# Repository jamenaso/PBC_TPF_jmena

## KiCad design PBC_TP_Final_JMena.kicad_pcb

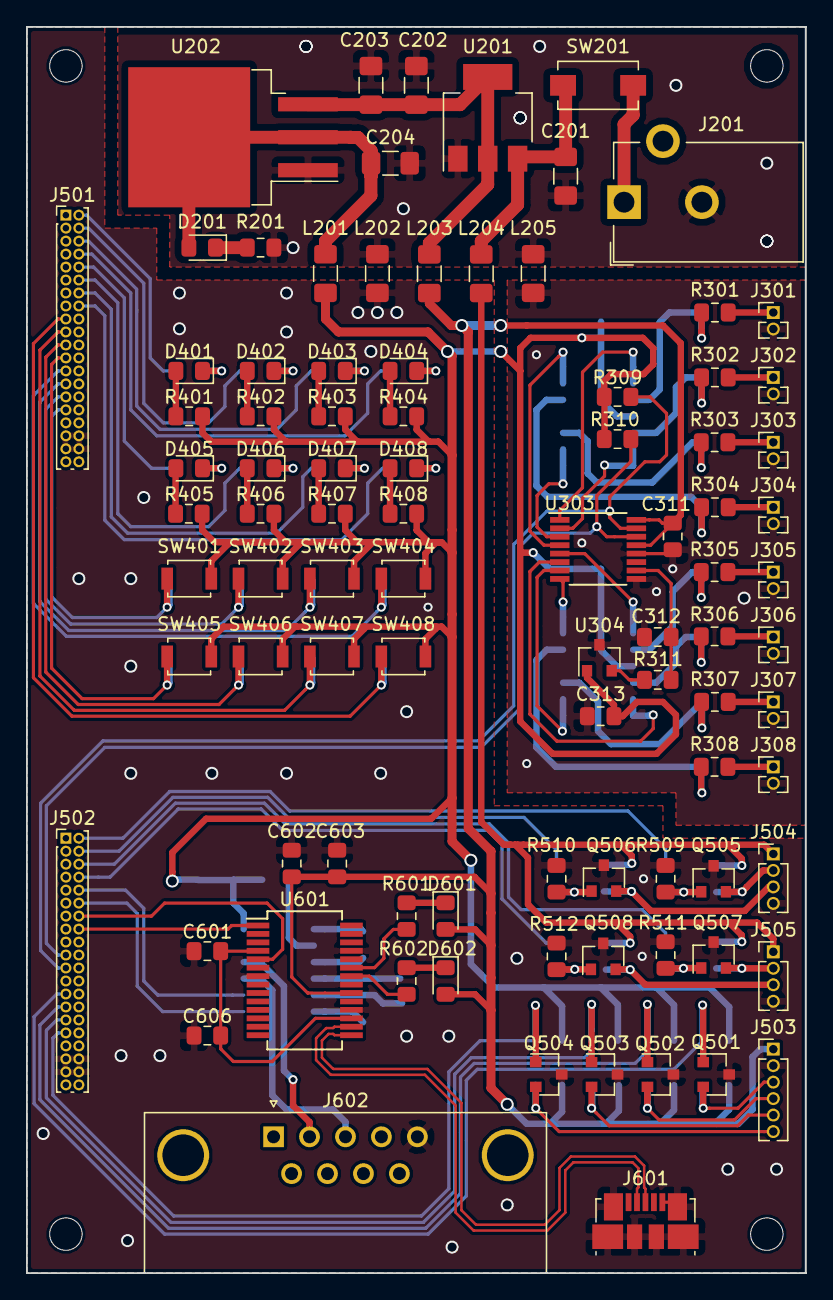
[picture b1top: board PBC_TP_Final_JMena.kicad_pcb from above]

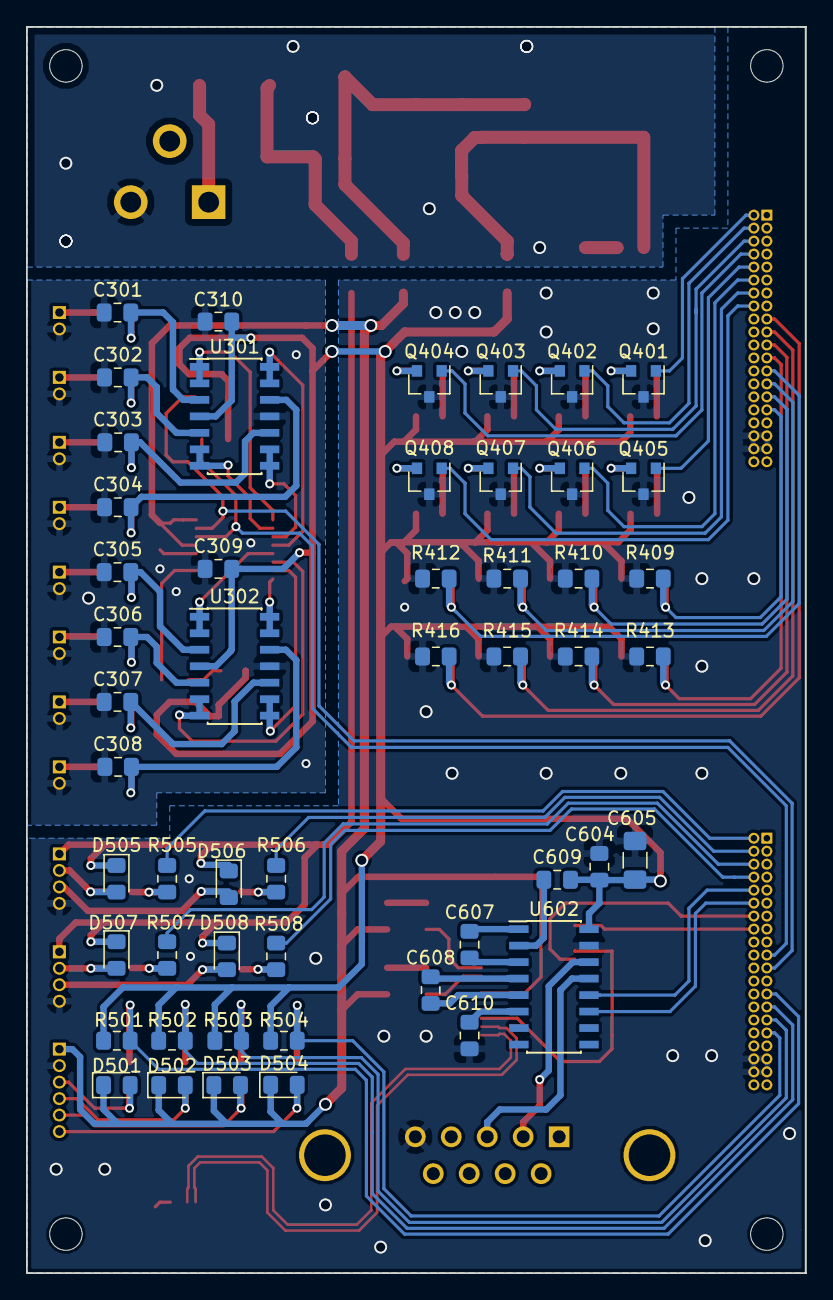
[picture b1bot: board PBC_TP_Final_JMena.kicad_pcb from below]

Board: 2 copper layers, 60.0 x 96.0 mm, 146 parts (51 on the bottom side), 110 nets.

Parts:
C201, C202, C203, C204: 10uF; C_1206_3216Metric_Pad1.42x1.75mm_HandSolder
C301, C302, C303, C304, C305, C306, C307, C308, C312, C603: 1uF; C_0805_2012Metric_Pad1.15x1.40mm_HandSolder
C309, C310, C311, C313, C601, C602, C604, C606, C607, C608, C609, C610: 0.1uF; C_0805_2012Metric_Pad1.15x1.40mm_HandSolder
C605: 2.2uF; C_1206_3216Metric_Pad1.42x1.75mm_HandSolder
D201, D401, D402, D403, D404, D405, D406, D407, D408, D601, D602: LED; LED_0805_2012Metric_Pad1.15x1.40mm_HandSolder
D501, D502, D503, D504, D505, D506, D507, D508: D_Schottky; D_0805_2012Metric_Pad1.15x1.40mm_HandSolder
J201: Barrel_Jack; BarrelJack_CUI_PJ-102AH_Horizontal
J301, J302, J303, J304, J305, J306, J307, J308: Conn_01x02_Female; PinHeader_1x02_P1.27mm_Vertical
J501, J502: Conn_01x40_Male; PinHeader_2x20_P1.00mm_Vertical
J503: Conn_01x06_Male; PinHeader_1x06_P1.27mm_Vertical
J504, J505: Conn_01x04; PinHeader_1x04_P1.27mm_Vertical
J601: USB_B_Micro; USB_Micro-B_Molex_47346-0001
J602: DB9_Male; DSUB-9_Male_Horizontal_P2.77x2.84mm_EdgePinOffset7.70mm_Hou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
L201, L202, L203, L204, L205: Ferrite_Bead; L_1206_3216Metric_Pad1.42x1.75mm_HandSolder
MH101, MH102, MH103, MH104: MountingHole; MountingHole_2.5mm
Q401, Q402, Q403, Q404, Q405, Q406, Q407, Q408, Q501, Q502, Q503, Q504, Q505, Q506, Q507, Q508: FDV301N; SOT-23
R201: 220; R_0805_2012Metric_Pad1.15x1.40mm_HandSolder
R301, R302, R303, R304, R305, R306, R307, R308: 10; R_0805_2012Metric_Pad1.15x1.40mm_HandSolder
R309, R310: 750; R_0805_2012Metric_Pad1.15x1.40mm_HandSolder
R311: 0; R_0805_2012Metric_Pad1.15x1.40mm_HandSolder
R401, R402, R403, R404, R405, R406, R407, R408: 470; R_0805_2012Metric_Pad1.15x1.40mm_HandSolder
R409, R410, R411, R412, R413, R414, R415, R416, R501, R502, R503, R504, R505, R506, R507, R508, R509, R510, R511, R512: 1K; R_0805_2012Metric_Pad1.15x1.40mm_HandSolder
R601, R602: 1K5; R_0805_2012Metric_Pad1.15x1.40mm_HandSolder
SW201: SW_DIP_x01; SW_SPST_EVQPE1
SW401, SW402, SW403, SW404, SW405, SW406, SW407, SW408: SW_Push; SW_SPST_B3U-1000P
U201: NCP1117-5.0_SOT223; SOT-223-3_TabPin2
U202: LM1084-3.3; TO-263-3_TabPin2
U301, U302: LM324; SOIC-14_3.9x8.7mm_P1.27mm
U303: ADS7828; TSSOP-16_4.4x5mm_P0.65mm
U304: MCP1525-TT; SOT-23
U601: FT232RL; SSOP-28_5.3x10.2mm_P0.65mm
U602: MAX3232; SOIC-16_3.9x9.9mm_P1.27mm

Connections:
+3V3: C309.1, C310.1, C313.1, C604.1, C605.1, C609.1, L201.1, R309.1, R310.1, R401.1, R402.1, R403.1, R404.1, R405.1, R406.1, R407.1, R408.1, R501.1, R502.1, R503.1, R504.1, SW401.2, SW402.2, SW403.2, SW404.2, SW405.2, SW406.2, SW407.2, SW408.2, U301.4, U302.4, U304.1, U602.16
+5V: C311.1, C602.1, C603.1, D501.1, D502.1, D503.1, D504.1, D601.2, D602.2, J503.1, L203.1, U303.13, U303.16, U601.20
+12V: D505.1, D506.1, D507.1, D508.1, J504.1, J505.1, L204.1
/Comunicación/COMM0: J502.16, U601.1
/Comunicación/COMM1: J502.14, U601.5
/Comunicación/COMM2: J502.12, U602.11
/Comunicación/COMM3: J502.10, U602.12
/Comunicación/D+: J601.3, U601.15
/Comunicación/D-: J601.2, U601.16
/Comunicación/RS232_RxIn: J602.3, U602.13
/Comunicación/RS232_TxOut: J602.2, U602.14
/Conversión Analogo-Digital/CH0: U301.1, U301.2, U303.1
/Conversión Analogo-Digital/CH1: U301.6, U301.7, U303.2
/Conversión Analogo-Digital/CH2: U301.8, U301.9, U303.3
/Conversión Analogo-Digital/CH3: U301.13, U301.14, U303.4
/Conversión Analogo-Digital/CH4: U302.1, U302.2, U303.5
/Conversión Analogo-Digital/CH5: U302.6, U302.7, U303.6
/Conversión Analogo-Digital/CH6: U302.8, U302.9, U303.7
/Conversión Analogo-Digital/CH7: U302.13, U302.14, U303.8
/Conversión Analogo-Digital/I2C0: J502.19, R310.2, U303.14
/Conversión Analogo-Digital/I2C1: J502.21, R309.2, U303.15
/Conversión Analogo-Digital/VREF: C312.1, R311.1, U303.10
/Fuente de Poder/IN12V: J201.1, SW201.1
/Fuente de Poder/PW3V3: C204.1, D201.2, L201.2, U202.2
/Fuente de Poder/PW5V: C202.1, C203.1, L203.2, U201.2, U202.3
/Fuente de Poder/PW12: C201.1, L204.2, SW201.2, U201.3
/Interfaz de Usuario/LED0: J501.2, Q401.1
/Interfaz de Usuario/LED1: J501.4, Q402.1
/Interfaz de Usuario/LED2: J501.6, Q403.1
/Interfaz de Usuario/LED3: J501.8, Q404.1
/Interfaz de Usuario/LED4: J501.10, Q405.1
/Interfaz de Usuario/LED5: J501.12, Q406.1
/Interfaz de Usuario/LED6: J501.14, Q407.1
/Interfaz de Usuario/LED7: J501.16, Q408.1
/Interfaz de Usuario/SW0: J501.31, R409.1, SW401.1
/Interfaz de Usuario/SW1: J501.29, R410.1, SW402.1
/Interfaz de Usuario/SW2: J501.27, R411.1, SW403.1
/Interfaz de Usuario/SW3: J501.25, R412.1, SW404.1
/Interfaz de Usuario/SW4: J501.23, R413.1, SW405.1
/Interfaz de Usuario/SW5: J501.21, R414.1, SW406.1
/Interfaz de Usuario/SW6: J501.19, R415.1, SW407.1
/Interfaz de Usuario/SW7: J501.17, R416.1, SW408.1
/Puertos de Entrada y Salida/CL0: J502.2, R505.2
/Puertos de Entrada y Salida/CL1: J502.6, R507.2
/Puertos de Entrada y Salida/CLOSE0: D505.2, J504.2, Q505.2
/Puertos de Entrada y Salida/CLOSE1: D507.2, J505.2, Q507.2
/Puertos de Entrada y Salida/OP0: J502.4, R506.2
/Puertos de Entrada y Salida/OP1: J502.8, R508.2
/Puertos de Entrada y Salida/OPEN0: D506.2, J504.3, Q506.2
/Puertos de Entrada y Salida/OPEN1: D508.2, J505.3, Q508.2
/Puertos de Entrada y Salida/PWM0: J502.25, Q501.1, R501.2
/Puertos de Entrada y Salida/PWM1: J502.27, Q502.1, R502.2
/Puertos de Entrada y Salida/PWM2: J502.29, Q503.1, R503.2
/Puertos de Entrada y Salida/PWM3: J502.31, Q504.1, R504.2
/Puertos de Entrada y Salida/PWM_OUT0: D501.2, J503.3, Q501.2
/Puertos de Entrada y Salida/PWM_OUT1: D502.2, J503.4, Q502.2
/Puertos de Entrada y Salida/PWM_OUT2: D503.2, J503.5, Q503.2
/Puertos de Entrada y Salida/PWM_OUT3: D504.2, J503.6, Q504.2
GNDA: C301.2, C302.2, C303.2, C304.2, C305.2, C306.2, C307.2, C308.2, C309.2, C310.2, C311.2, C312.2, C313.2, J301.2, J302.2, J303.2, J304.2, J305.2, J306.2, J307.2, J308.2, L205.1, U301.11, U302.11, U303.9, U303.12, U304.3
GNDD: C601.2, C602.2, C603.2, C604.2, C605.2, C606.2, C610.2, J501.35, J501.36, J501.37, J501.38, J502.35, J502.36, J502.37, J502.38, J503.2, J504.4, J505.4, J601.5, J601.6, J602.5, L202.1, Q401.3, Q402.3, Q403.3, Q404.3, Q405.3, Q406.3, Q407.3, Q408.3, Q501.3, Q502.3, Q503.3, Q504.3, Q505.3, Q506.3, Q507.3, Q508.3, R409.2, R410.2, R411.2, R412.2, R413.2, R414.2, R415.2, R416.2, R509.2, R510.2, R511.2, R512.2, U601.7, U601.18, U601.21, U601.25, U602.15
GNDPWR: C201.2, C202.2, C203.2, C204.2, J201.2, L202.2, L205.2, R201.2, U201.1, U202.1
unnamed: C301.1, R301.1, U301.3
unnamed: C302.1, R302.1, U301.5
unnamed: C303.1, R303.1, U301.10
unnamed: C304.1, R304.1, U301.12
unnamed: C305.1, R305.1, U302.3
unnamed: C306.1, R306.1, U302.5
unnamed: C307.1, R307.1, U302.10
unnamed: C308.1, R308.1, U302.12
unnamed: C601.1, C606.1, U601.4, U601.17
unnamed: C607.1, U602.1
unnamed: C607.2, U602.3
unnamed: C608.1, U602.4
unnamed: C608.2, U602.5
unnamed: C609.2, U602.2
unnamed: C610.1, U602.6
unnamed: D201.1, R201.1
unnamed: D401.1, Q401.2
unnamed: D401.2, R401.2
unnamed: D402.1, Q402.2
unnamed: D402.2, R402.2
unnamed: D403.1, Q403.2
unnamed: D403.2, R403.2
unnamed: D404.1, Q404.2
unnamed: D404.2, R404.2
unnamed: D405.1, Q405.2
unnamed: D405.2, R405.2
unnamed: D406.1, Q406.2
unnamed: D406.2, R406.2
unnamed: D407.1, Q407.2
unnamed: D407.2, R407.2
unnamed: D408.1, Q408.2
unnamed: D408.2, R408.2
unnamed: D601.1, R601.1
unnamed: D602.1, R602.1
unnamed: J301.1, R301.2
unnamed: J302.1, R302.2
unnamed: J303.1, R303.2
unnamed: J304.1, R304.2
unnamed: J305.1, R305.2
unnamed: J306.1, R306.2
unnamed: J307.1, R307.2
unnamed: J308.1, R308.2
unnamed: Q505.1, R505.1, R509.1
unnamed: Q506.1, R506.1, R510.1
unnamed: Q507.1, R507.1, R511.1
unnamed: Q508.1, R508.1, R512.1
unnamed: R311.2, U304.2
unnamed: R601.2, U601.23
unnamed: R602.2, U601.22

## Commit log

2018-09-25 Se crea el repositorio con archivo esquematico
2018-10-17 Se hace cambios en el esquematico y se anexa PCB
2018-10-17 Se agrega plantilla
2018-11-15 Se realizan correcciones finales y se agregan carpetas BOM, Datasheet, Doc, Gerbers, lib.pretty y shapes3D
